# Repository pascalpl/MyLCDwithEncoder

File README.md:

MyLCDwithEncoder is my variation of RepRapDiscount Panel without SDcard reader.
MyLCDwithEncoder has buzzer, rotaty encoder with press button and slot for LCD (hd44780) 4x16/4x20 or 2x16.
PCB is very easy to made it home. Single layer PCB.

Library for Eagle in lbr/ folder.

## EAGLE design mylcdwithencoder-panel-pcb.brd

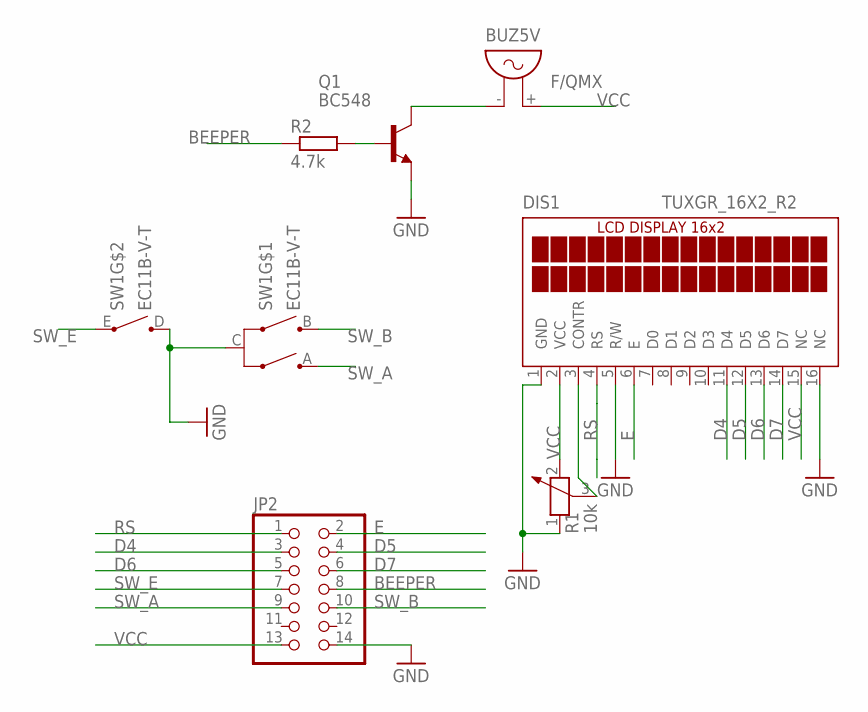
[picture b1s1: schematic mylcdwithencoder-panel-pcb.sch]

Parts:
BUZ5V: F/QMX
DIS1: TUXGR_16X2_R2
JP2: PINHD-2X7; 2X07
Q1: BC548; TO92-EBC
R1: 10k; PT-10
R2: 4.7k; 0207/10
SW1: EC11B-V-T; EC11B-V

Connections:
BEEPER: JP2.8, R2.1
D4: DIS1.11 (D4), JP2.3
D5: DIS1.12 (D5), JP2.4
D6: DIS1.13 (D6), JP2.5
D7: DIS1.14 (D7), JP2.6
E: DIS1.6 (E), JP2.2
GND: DIS1.1 (GND), DIS1.5 (R/W), DIS1.16 (NC), JP2.14, Q1.E, R1.1, SW1.C, SW1.D
unnamed: DIS1.3 (CONTR), R1.3
unnamed: Q1.B, R2.2
unnamed: BUZ5V.- (1), Q1.C
RS: DIS1.4 (RS), JP2.1
SW_A: JP2.9, SW1.A
SW_B: JP2.10, SW1.B
SW_E: JP2.7, SW1.E
VCC: BUZ5V.+ (2), DIS1.2 (VCC), DIS1.15 (NC), JP2.13, R1.2

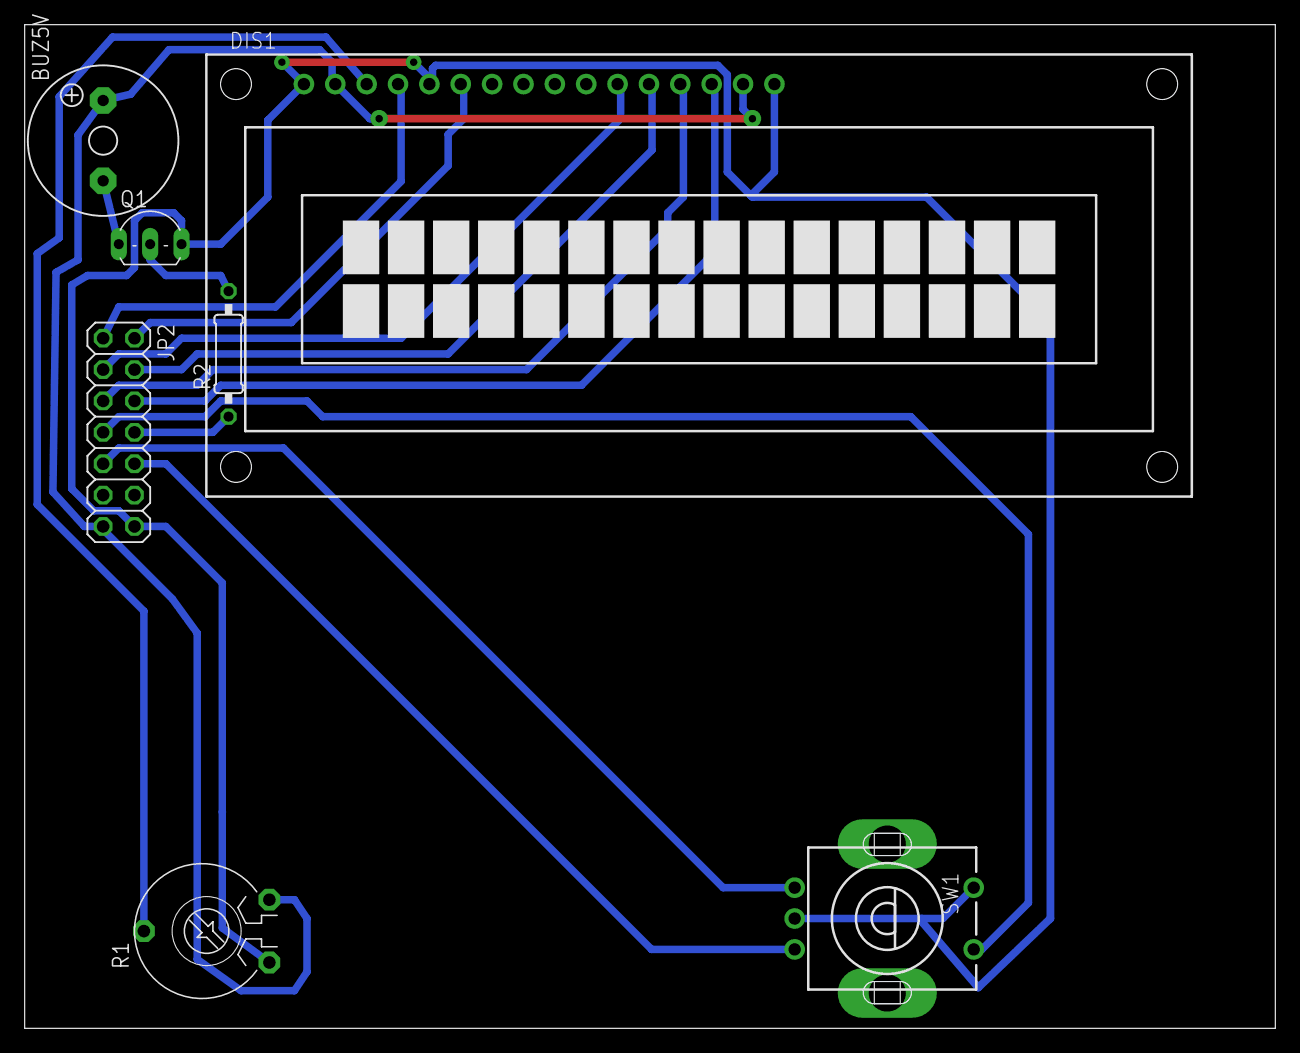
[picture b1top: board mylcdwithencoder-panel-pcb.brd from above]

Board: 2 copper layers, 101.3 x 81.3 mm, 7 parts (0 on the bottom side), 15 nets.

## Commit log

2014-04-16 MyLCDwithEncoder is my version of RepRapDiscount Panel without SDcard reader. Raedy for home PCB manufacturing. Single layer PCB.
2014-04-17 modified: README.md
    Little photo documentation:
    new file: pic/MLE01.jpg
    new file: pic/MLE02.jpg
    new file: pic/MLE03.jpg
    new file: pic/MLE04.jpg
    new file: pic/MLE05.jpg
2014-04-17 deleted: lbr/SD.lbr deleted: lbr/lm1117.lbr
